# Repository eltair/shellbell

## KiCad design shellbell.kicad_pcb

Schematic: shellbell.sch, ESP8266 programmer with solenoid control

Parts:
C1: 100uF; CP_Radial_D6.3mm_P2.50mm
C2, C3: 10uf; CP_Radial_D5.0mm_P2.00mm
C4: C; C_1206_3216Metric
D1, D4, D5: D; D_DO-41_SOD81_P7.62mm_Horizontal
D2, D3: LED; D_1206_3216Metric
D6, D7: 1N4148W; D_SOD-123
H1: MountingHole_Pad; MountingHole_2.2mm_M2_Pad_Via
J1: Barrel_Jack_MountingPin; BarrelJack_CUI_PJ-063AH_Horizontal
J2: Conn_02x04_Odd_Even; PinSocket_2x04_P2.54mm_Vertical
J3: USB_B_Mini; USB_Mini-B_Lumberg_2486_01_Horizontal
L1: Solenoid; PinHeader_1x02_P2.54mm_Vertical
Q1: IRLB8721PBF; TO-252-2
R1, R2, R3: 3.3k; R_1206_3216Metric
R4, R5: 330; R_1206_3216Metric
S2: GPIO0; SW_B3U-3000P
S3: RST; SW_B3U-3000P
U1: LD1117V33; TO-220-3_Vertical; MPN LD1117V33; Digi-Key_PN 497-1491-5-ND
U2: FT230XS-U; SSOP-16_W3.90mm; MPN FT230XS-U; Digi-Key_PN 768-1154-5-ND

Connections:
+3V3: C2.1, D2.2 (A), J2.8, R1.2, R2.1, R3.1, R5.2, U1.2 (VOUT), U2.11 (RESET)
+5V: C3.1, C4.1, D4.2 (A), D6.1 (K), J3.1 (VBUS), U2.12 (VCC)
+12V: C1.1, D1.1 (K), D5.2 (A), D7.1 (K), J1.1, L1.1
/CH_PD: J2.4, R2.2
/CTL: J2.3, Q1.1 (G)
/GPIO0: J2.5, R1.1, S2.1
/LGND: D1.2 (A), L1.2, Q1.2 (D)
/RST: J2.6, R3.2, S3.1
/RXD: J2.2, U2.4 (RXD)
/RX_LED#: R4.1, U2.14 (CBUS1)
/TXD: J2.7, U2.1 (TXD)
/TX_LED#: D3.1 (K), U2.7 (CBUS2)
/USBDM: J3.2 (D-), U2.9 (USBDM)
/USBDP: J3.3 (D+), U2.8 (USBDP)
/VCCIO: U2.3 (VCCIO), U2.10 (3V3OUT)
GND: C1.2, C2.2, C3.2, C4.2, D6.2 (A), D7.2 (A), H1.1, J1.2, J1.MP (MountPin), J2.1, J3.5 (GND), J3.6 (Shield), Q1.3 (S), S2.2, S3.2, U1.1 (GND), U2.5 (GND), U2.13 (GND)
unnamed: D2.1 (K), R4.2
unnamed: D3.2 (A), R5.1
unnamed: D4.1 (K), D5.1 (K), U1.3 (VIN)

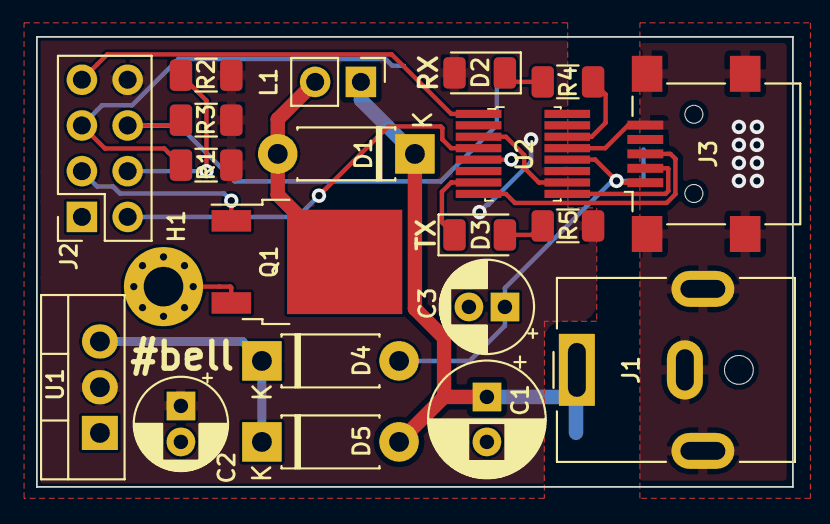
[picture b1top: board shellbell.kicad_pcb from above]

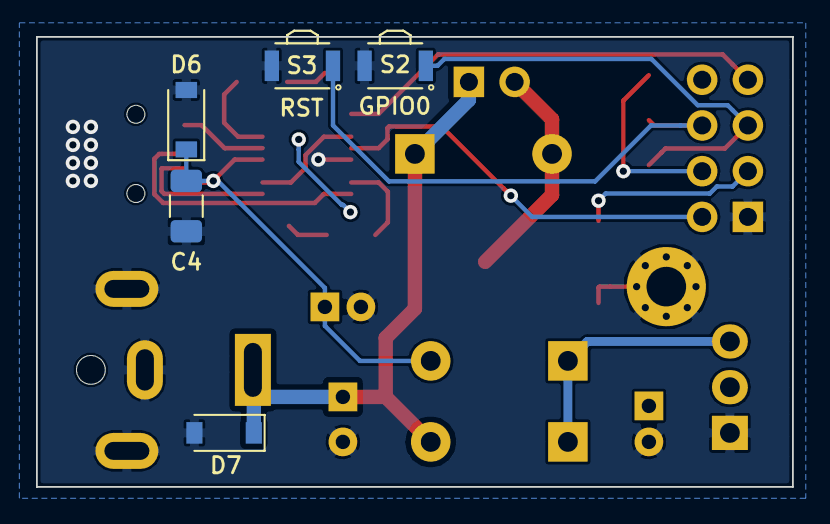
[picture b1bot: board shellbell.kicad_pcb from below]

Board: 2 copper layers, 42.0 x 25.0 mm, 26 parts (5 on the bottom side), 19 nets.

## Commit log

2019-03-25 Import v1.
2019-04-04 Import v2 with usb programming circuit.
2019-05-24 Fixes TX/RX. Removes RTS-reset. Clean up.
2019-05-24 Add gerbers.zip.
2019-05-31 Add programming buttons and rerouting.
